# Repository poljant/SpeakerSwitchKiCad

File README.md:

# SpeakerSwitchKiCad
PCB Speaker Switch.

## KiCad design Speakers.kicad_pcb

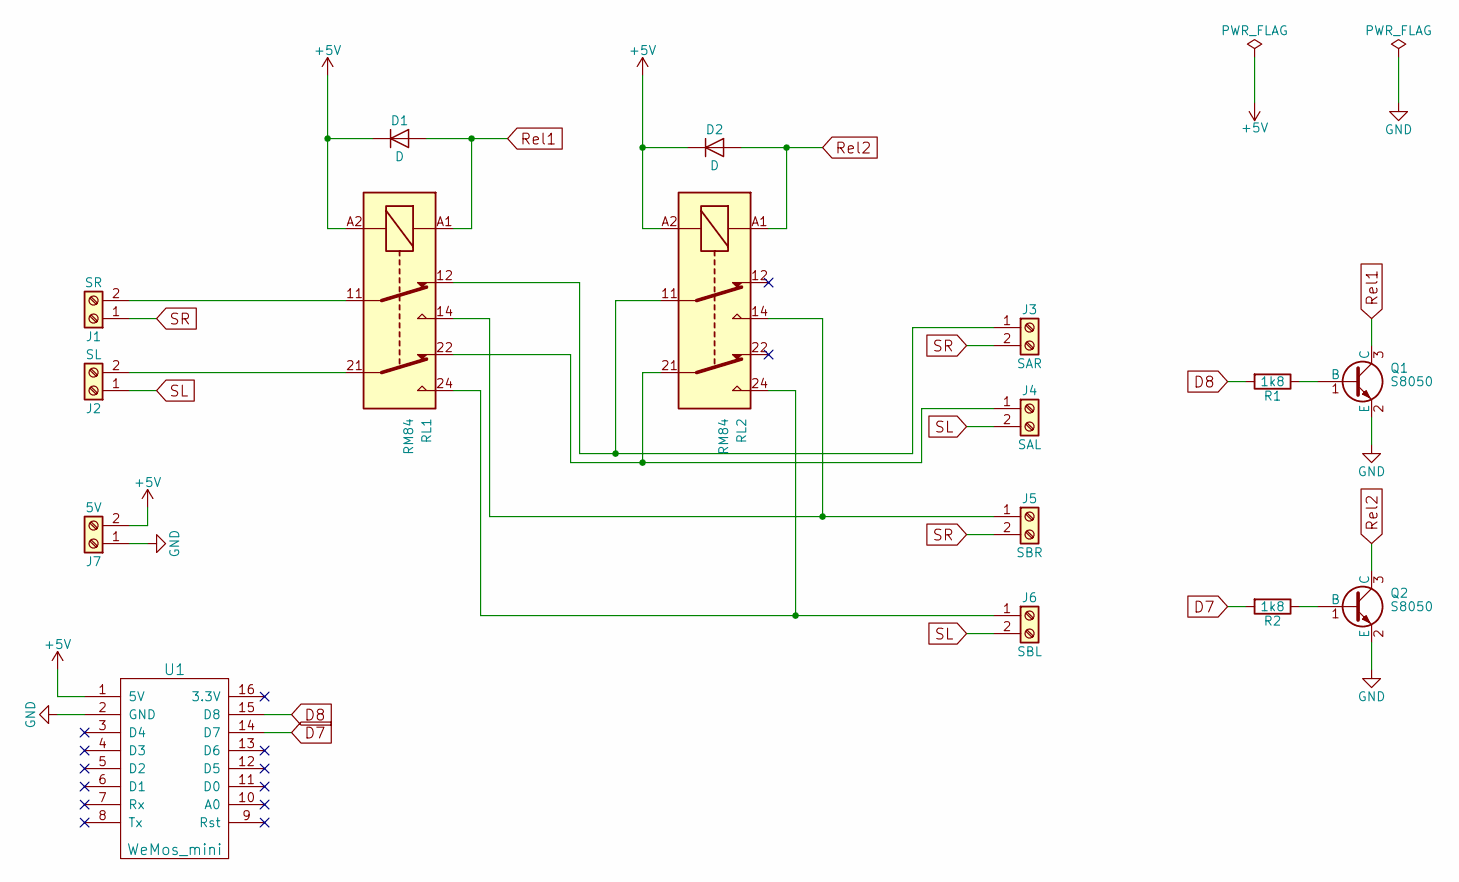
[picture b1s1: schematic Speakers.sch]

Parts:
D1, D2: D; D_1206
J1: SR; gmkds_3-2-5
J2: SL; gmkds_3-2-5
J3: SAR; gmkds_3-2-5
J4: SAL; gmkds_3-2-5
J5: SBR; gmkds_3-2-5
J6: SBL; gmkds_3-2-5
J7: 5V; gmkds_3-2-5
Q1, Q2: S8050; SOT-23_Handsoldering
R1, R2: 1k8; R_1206_HandSoldering
RL1, RL2: RM84; Relay_DPDT_Finder_40.52
U1: WeMos_mini; D1_mini_board

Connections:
+5V: D1.1 (K), D2.1 (K), J7.2, RL1.A2, RL2.A2, U1.1 (5V)
D7: R2.2, U1.14 (D7)
D8: R1.2, U1.15 (D8)
GND: J7.1, Q1.2 (E), Q2.2 (E), U1.2 (GND)
unnamed: J1.2, RL1.11
unnamed: J2.2, RL1.21
unnamed: J3.1, RL1.12, RL2.11
unnamed: J4.1, RL1.22, RL2.21
unnamed: J5.1, RL1.14, RL2.14
unnamed: J6.1, RL1.24, RL2.24
unnamed: Q1.1 (B), R1.1
unnamed: Q2.1 (B), R2.1
Rel1: D1.2 (A), Q1.3 (C), RL1.A1
Rel2: D2.2 (A), Q2.3 (C), RL2.A1
SL: J2.1, J4.2, J6.2
SR: J1.1, J3.2, J5.2

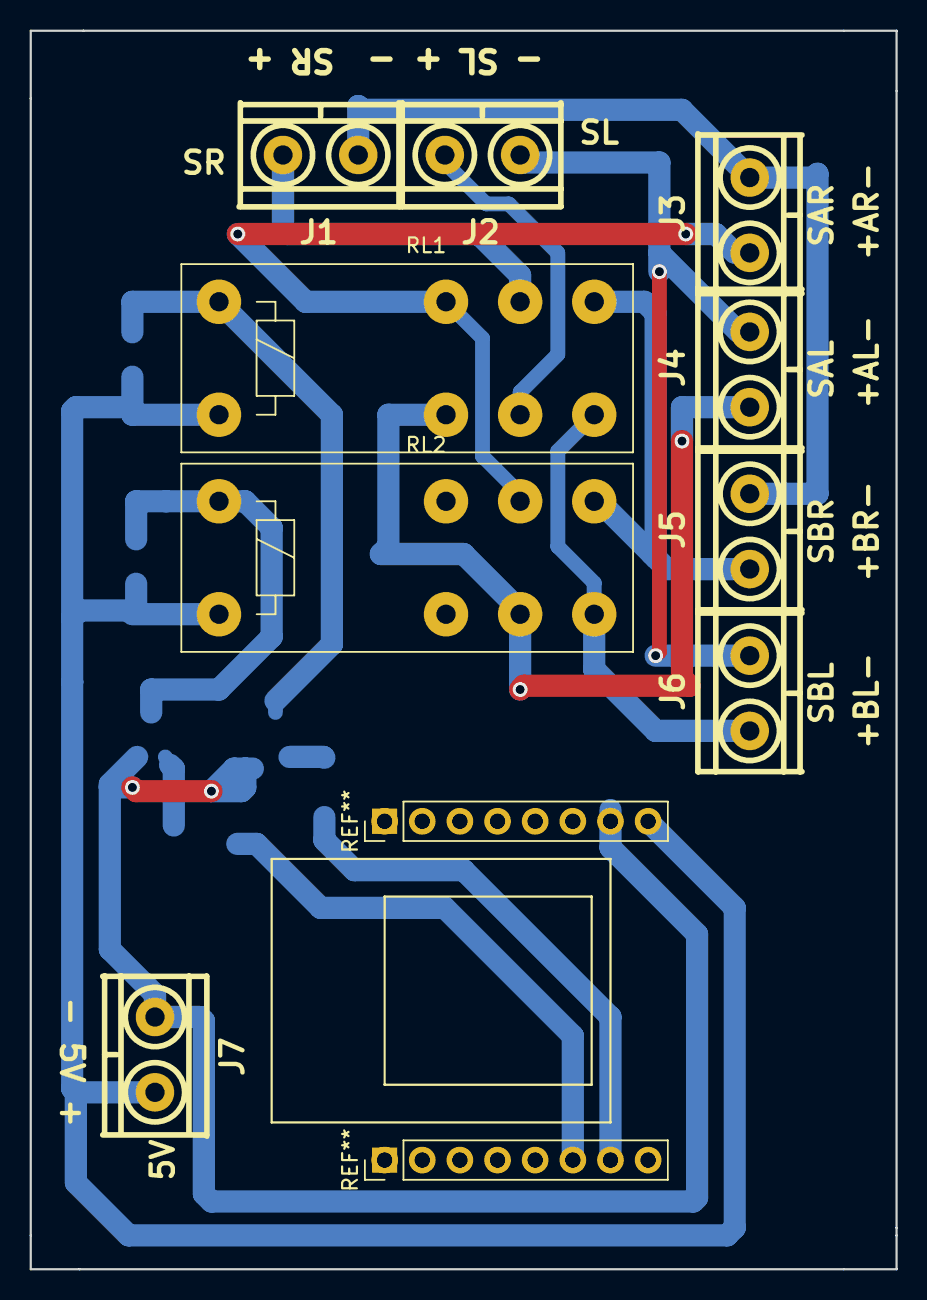
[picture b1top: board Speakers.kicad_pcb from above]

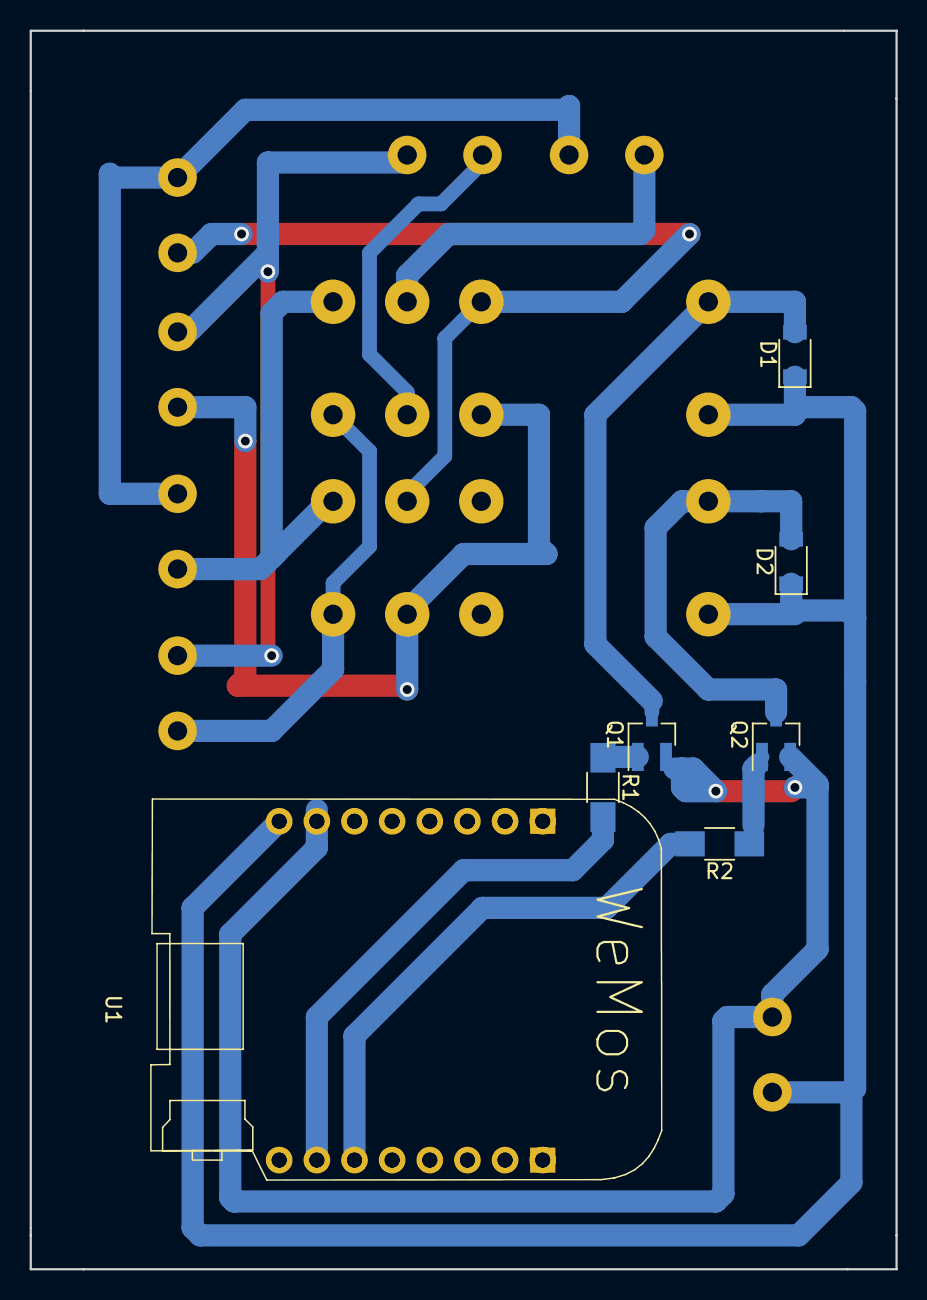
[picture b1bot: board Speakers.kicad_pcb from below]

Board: 2 copper layers, 58.4 x 83.6 mm, 16 parts (7 on the bottom side), 16 nets.

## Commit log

2018-08-15 Stan początkowy
2018-08-16 Zmiana wartości R1 i R2
2018-08-26 dodano plik .pdf schematu
2018-08-27 dodano plik pdf z PCB
2018-08-27 dodano opisy przy złączkach na warstwie górnej
2018-08-27 drobne porawki opisów
2018-08-28 usunięto biblioteki sygnalizujęce błąd
2018-08-28 drobne uzupełniena
